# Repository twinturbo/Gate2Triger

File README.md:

# Gate2Triger

This is a Quad Kosmo Format Gate to Trigger Module , only fit RV1 or R1. RV1 is really for initial tweeking of the trigger point the fixed resistor can be used instead.
Ideally you should use a dual trace scope to get your trigger nice and sharp.

It's named "The LLoyd Peck" after the famous british actor who played Trigger in the TV Show "Only Fools and Horses"

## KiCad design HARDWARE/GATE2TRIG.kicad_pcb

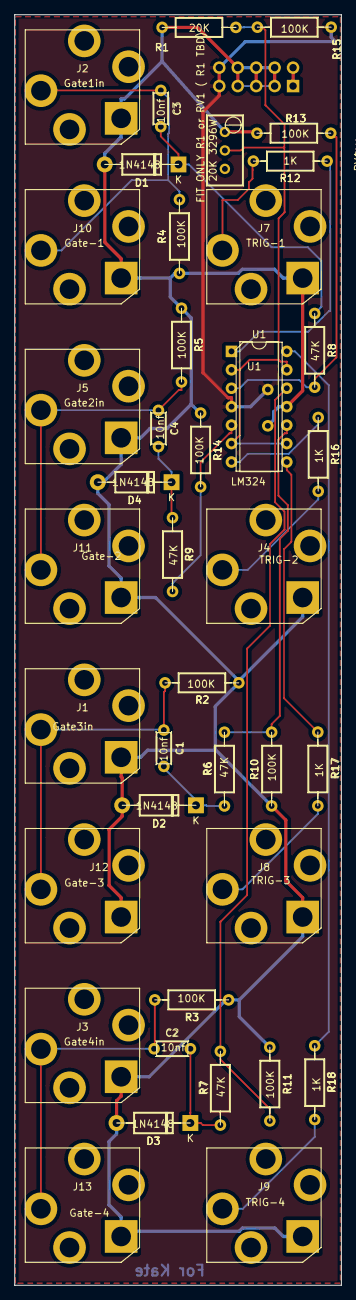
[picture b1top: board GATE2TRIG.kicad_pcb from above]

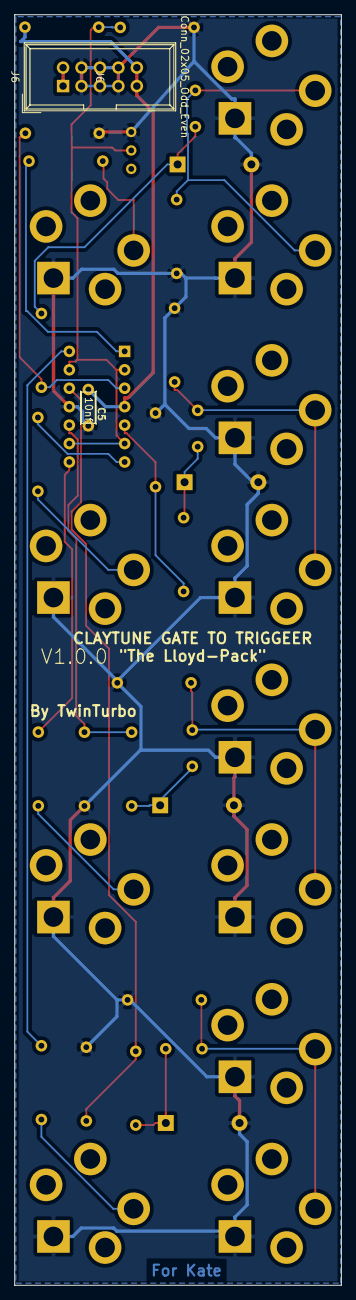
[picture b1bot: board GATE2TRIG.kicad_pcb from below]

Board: 2 copper layers, 45.0 x 175.0 mm, 42 parts (2 on the bottom side), 24 nets.

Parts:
C1, C2, C3, C4, C5: 10nf; C_Disc_D4.3mm_W1.9mm_P5.00mm
D1, D2, D3, D4: 1N4148; D_DO-41_SOD81_P10.16mm_Horizontal
J1: Gate3in; Jack_6.5mmLMNC
J2: Gate1in; Jack_6.5mmLMNC
J3: Gate4in; Jack_6.5mmLMNC
J4: TRIG-2; Jack_6.5mmLMNC
J5: Gate2in; Jack_6.5mmLMNC
J6: Conn_02x05_Odd_Even; IDC-Header_2x05_P2.54mm_Vertical
J7: TRIG-1; Jack_6.5mmLMNC
J8: TRIG-3; Jack_6.5mmLMNC
J9: TRIG-4; Jack_6.5mmLMNC
J10: Gate-1; Jack_6.5mmLMNC
J11: Gate-2; Jack_6.5mmLMNC
J12: Gate-3; Jack_6.5mmLMNC
J13: Gate-4; Jack_6.5mmLMNC
R1: 20K; R_Axial_DIN0207_L6.3mm_D2.5mm_P10.16mm_Horizontal
R2, R3, R4, R5, R10, R11, R13, R14, R15: 100K; R_Axial_DIN0207_L6.3mm_D2.5mm_P10.16mm_Horizontal
R6, R7, R8, R9: 47K; R_Axial_DIN0207_L6.3mm_D2.5mm_P10.16mm_Horizontal
R12, R16, R17, R18: 1K; R_Axial_DIN0207_L6.3mm_D2.5mm_P10.16mm_Horizontal
RV1: 20K 3296W; Potentiometer_Bourns_3296W_Vertical
U1: LM324; DIP-14_W7.62mm

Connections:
+12V: C5.1, J6.9, J6.10, R15.2, U1.4
-12V: J6.1, J6.2
GND: C5.2, D1.2, D2.2, D3.2, D4.2, J1.G, J2.G, J3.G, J4.G, J5.G, J6.3, J6.4, J6.5, J6.6, J6.7, J6.8, J7.G, J8.G, J9.G, J10.G, J11.G, J12.G, J13.G, R1.1, R2.1, R3.1, R4.1, R5.1, R10.1, R11.1, R13.1, R14.1, RV1.1, U1.11
Gate1: C3.1, J2.T, J10.T, R4.2
Gate2: C4.1, J5.T, J11.T, R5.2
Gate3: C1.1, J1.T, J12.T, R2.2
Gate4: C2.1, J3.T, J13.T, R3.2
unnamed: C1.2, D2.1, R6.1
unnamed: C2.2, D3.1, R7.1
unnamed: C3.2, D1.1, R8.1
unnamed: C4.2, D4.1, R9.1
unnamed: R1.2, R15.1, RV1.2, U1.2, U1.6, U1.9, U1.13
unnamed: R12.1, U1.1
unnamed: R16.1, U1.7
unnamed: R17.1, U1.8
unnamed: R18.1, U1.14
T1: R8.2, R13.2, U1.3
T2: R9.2, R14.2, U1.5
T3: R6.2, R10.2, U1.10
T4: R7.2, R11.2, U1.12
Trig1: J7.T, R12.2
Trig2: J4.T, R16.2
Trig3: J8.T, R17.2
Trig4: J9.T, R18.2

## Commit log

2020-12-25 Initialised
2020-12-25 Clean
2020-12-26 autosync
2022-01-30 RC300122
2022-02-07 Combined
2022-02-20 PICS
2022-02-25 tohome
2023-05-25 holidaysync
